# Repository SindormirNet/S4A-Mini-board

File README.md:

<p align="center">

<div align="center"><i>S4A Mini board render.</i></div>
</p>  

S4A Mini Board
========================================

Esta placa es una shield para su uso con Arduino, con el fin de proporcionar de forma cómoda y rápida acceso a los siguientes sensores y actuadores:

-   Entradas:
    +   Dos potenciómetros.
    +   Dos pulsadores.
    +   Una LDR.
-   Salidas:
    +   Dos servomotores.
    +   Dos LED en modo digital.
    +   Un LED en modo PWM.
    +   Un zumbador.
-   Conexiones:
    +   Cabeceras de conexión para Arduino UNO.
    +   Pines de alimentación (5V y GND).
    +   Pines de E/S de Arduino no utilizados por la shield. Pines A3, A4, A5, 5, 6, 8 y 11 

Es compatible con placas Arduino con capacidad para shield, como las placas UNO, Leonardo o Mega. No requiere la instalación de ninguna librería específica.

<p align="center">

<div align="center"><i>S4A Mini board real (v0.1).</i></div>
</p>

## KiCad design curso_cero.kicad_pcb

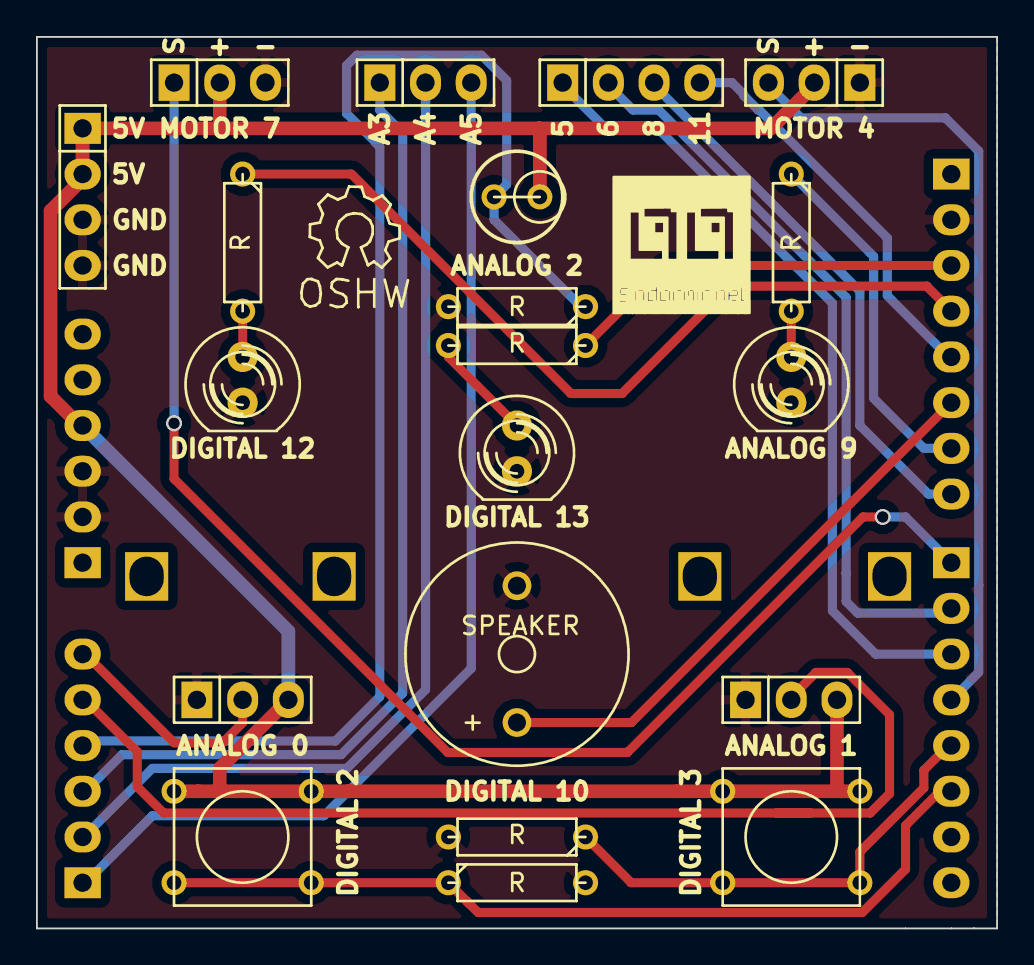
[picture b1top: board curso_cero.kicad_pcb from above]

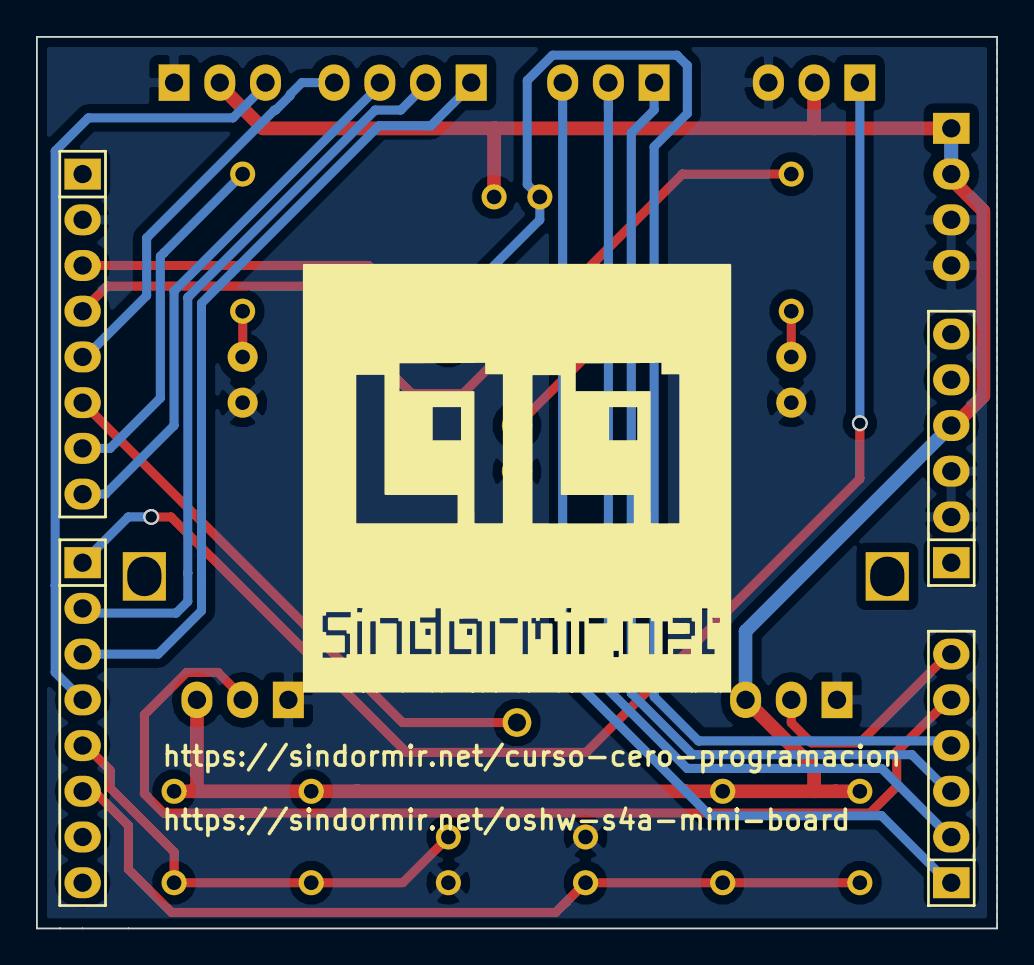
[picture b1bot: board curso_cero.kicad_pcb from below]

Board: 2 copper layers, 53.3 x 49.5 mm, 27 parts (4 on the bottom side), 23 nets.

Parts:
1pin, 1pin#2: VAL**; 1pin
D1, D2, D3: LED; LED-5MM
P1, P2: CONN_01X06; Pin_Header_Straight_1x06
P3: CONN_01X03; Socket_Strip_Straight_1x03
P4, P9: CONN_01X04; Socket_Strip_Straight_1x04
P5, P6: CONN_01X03; Pin_Header_Straight_1x03
P7, P8: CONN_01X08; Pin_Header_Straight_1x08
R1, R2, R3, R4, R5, R7: R; R3
R6: R; R1
RV1, RV2: POT; Pin_Header_Straight_1x03
SP1: SPEAKER; MagneticBuzzer_ProSignal_ABI-009-RC
SW1, SW2: SW_PUSH; SW_PUSH_SMALL
Symbol_OSHW-Logo_SilkScreen: VAL**; Symbol_OSHW-Logo_SilkScreen

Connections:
5V: P1.4, P5.2, P6.2, P9.1, P9.2, R6.1, RV1.3, RV2.3, SW1.1, SW2.1
GND: D1.2, D2.2, D3.2, P1.2, P1.3, P5.1, P6.3, P7.2, P9.3, P9.4, R2.2, R4.2, R7.2, RV1.1, RV2.1, SP1.2
unnamed: D1.1, R1.2
unnamed: D2.1, R3.2
unnamed: D3.1, R5.2
PIN2: P8.6, R2.1, SW1.2
PIN3: P8.5, R4.1, SW2.2
PIN4: P5.3, P8.4
PIN5: P4.1, P8.3
PIN6: P4.2, P8.2
PIN7: P6.1, P8.1
PIN8: P4.3, P7.8
PIN9: P7.7, R1.1
PIN10: P7.6, SP1.1
PIN11: P4.4, P7.5
PIN12: P7.4, R5.1
PIN13: P7.3, R3.1
PINA0: P2.6, RV1.2
PINA1: P2.5, RV2.2
PINA2: P2.4, R6.2, R7.1
PINA3: P2.3, P3.1
PINA4: P2.2, P3.2
PINA5: P2.1, P3.3

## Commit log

2015-02-24 Versión inicial. Placa funcional 100%
2015-02-25 Añadido README y subida foto de la placa
2017-03-22 Cambios para las nuevas versiones de Kicad. Corregidos fallos estéticos
2017-04-28 cambiados footprints por reemplazos de nueva librería kicad
2017-04-28 recolocado esquematico, corregida polaridad de conectores y buzzer
2017-04-28 editado recuadro de esquematico
2017-04-28 eliminadas librerias de esquematico huerfanas
2017-04-28 regenerada netlist
2017-04-29 añadidos valores de LED segun color
2017-04-29 corregido error en polaridad de conector entradas analogicas
2017-04-29 corregido nombre de net pin D10
2017-04-29 cambiado valores pulsadores
2017-04-29 comprobado y recolocada posicion cabeceras Arduino, añadidas cotas en mil, optimizacion de trazado, rellenado recuadro de datos de PCB, editadas clases de nets, reubicados nuevos footprints de boton 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
2017-04-29 renombrados archivos segun nombre pcb
2017-04-29 editado README
2017-04-29 modificada ruta de imagen en README
